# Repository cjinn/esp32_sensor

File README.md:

# ESP32 Sensor Module
This repository outlines an attempt to make a universal ESP32 board to conduct IoT projects with the help of sensors. As such, it is highly customisable and will most likely undergo many revisions.

The goal is to have multiple of these ESP32 sensor modules interact with each other using mesh Wi-Fi to share information with each other.

# Table of Contents
- [ESP32 Sensor Module](#esp32-sensor-module)
- [Table of Contents](#table-of-contents)
- [Hardware Versions](#hardware-versions)
  - [v0.0.3b](#v003b)
    - [v0.0.3c](#v003c)
    - [Known Hardware Issues](#known-hardware-issues)
- [Acknowledgements](#acknowledgements)

# Hardware Versions
Each hardware revision will be updated and the version as such. This version system is adopted from v0.0.4 onwards. The convection is as follows:

X.Y.ZA
- X: Major version number of the design. It is assumed there are major changes to the overall design including PCB, components, fucntionality, purpose, etc.
- Y: Minor version number of the design. Any increment on this signifies a minor design revision. Most likely an electrical characteristic change and/or component replacement.
- Z: Revision version number of the design. Any increment on this signifies a commit has been made to the design. Most likely adjustments to facilitate assembly houses, manufacturing and production.
- A: Alphabetical designation. Used to indicate even more minor adjustments like spelling mistakes and refreshing files.

## v0.0.3b
Originally a 4-layer PCB, it was redesigned to a 2-layer PCB in order to meet capstone project deadlines and it is the first iteration that was manufactured, tested and worked (well, most of it anyways). As such, it is noticebly bare-bones and has hardware design flaws. It is not recommended to go with this.

### v0.0.3c
Refreshed gerber files, schematics and BOM to be packaged such that it can be used to shop around between assembly houses. No meaningful changes since v0.0.3b.

### Known Hardware Issues
- [IMU SDA pin interferes with ESP32 boot up](https://github.com/cjinn/esp32_sensor/issues/2)
- [Crystal Oscillator missing from Hardware Design](https://github.com/cjinn/esp32_sensor/issues/1)

# Acknowledgements
Thanks to Isaac Tan for helping me design, test and realise this project from the very beginning.

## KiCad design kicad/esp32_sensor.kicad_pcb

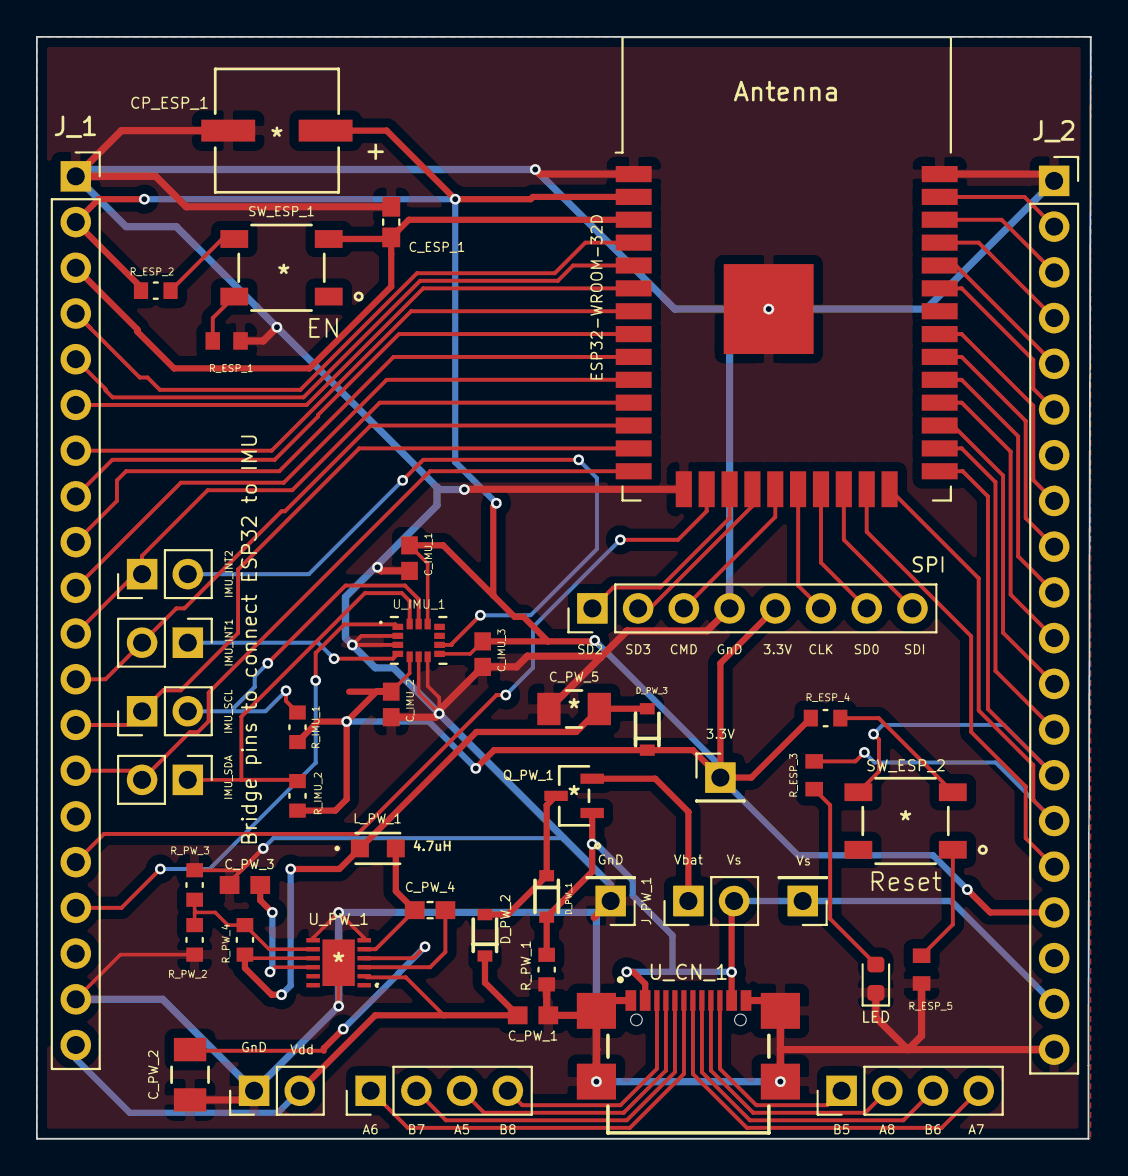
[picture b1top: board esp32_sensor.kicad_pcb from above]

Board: 2 copper layers, 58.5 x 61.2 mm, 47 parts (0 on the bottom side), 63 nets.

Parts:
CP_ESP_1: 100uF; UCB0J101MCL1GS
C_ESP_1: 0.1uF; CAPC1608X90
C_IMU_1, C_IMU_2, C_IMU_3: 100nF; CAPC1608X90N
C_PW_1, C_PW_3: 1uF; 0603
C_PW_2, C_PW_5: 4.7uF; C1206C475K3RACAUTO
C_PW_4: 0.1uF; CAPC1608X90
D_PW_1, D_PW_2, D_PW_3: BAT20JFILM
J_1, J_2: 4157; PinSocket_1x20_P2.54mm_Vertical
J_3: SPI; PinHeader_1x08_P2.54mm_Vertical
J_4: IMU_INT2; PinHeader_1x02_P2.54mm_Vertical
J_5: IMU_INT1; PinHeader_1x02_P2.54mm_Vertical
J_6: IMU_SCL; PinHeader_1x02_P2.54mm_Vertical
J_7: IMU_SDA; PinHeader_1x02_P2.54mm_Vertical
J_CN_1, J_CN_2: Header_Pin_4; PinHeader_1x04_P2.54mm_Vertical
J_CN_3, J_CN_4: Header_Pin_1; PinHeader_1x01_P2.54mm_Vertical
J_PW_1, J_PW_2: Header_Pin_2; PinHeader_1x02_P2.54mm_Vertical
J_PW_3: Header_Pin_1; PinHeader_1x01_P2.54mm_Vertical
LED_ESP_1: LED; LED_0603_1608Metric
L_PW_1: 4.7uH; CV201210-4R7K
Q_PW_1: IRLML5103TRPBF
R_ESP_1, R_ESP_3, R_ESP_5: 500; RESC1508X55N
R_ESP_2, R_ESP_4: 10k; RESC1608X55N
R_IMU_1, R_IMU_2: 4.7k; RESC1608X55N
R_PW_1: 10k; RESC1608X55N
R_PW_2, R_PW_3: 100k; RESC1608X55N
R_PW_4: 115k; RESC1608X55N
SW_ESP_1, SW_ESP_2: PTS647SK38SMTR2LFS
U_CN_1: USB4110-GF-A
U_ESP_1: ESP32-WROOM-32D; ESP32-WROOM-32
U_IMU_1: LSM6DSMTR
U_PW_1: MAX25276ATCA_VY+; MAX25276ATCAVY

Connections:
+3V3: CP_ESP_1.1, C_IMU_1.1, C_IMU_2.1, C_IMU_3.1, D_PW_3.C, J_1.2, J_2.17, J_3.5, J_PW_3.1, R_ESP_2.1, R_ESP_4.2, R_IMU_1.2, R_IMU_2.1, U_ESP_1.2, U_IMU_1.5, U_IMU_1.8, U_IMU_1.12
+BATT: J_PW_1.1, Q_PW_1.2
/ESP32 Chip/ESP32_EN: C_ESP_1.1, J_1.3, SW_ESP_1.3, U_ESP_1.3
/ESP32 Chip/ESP32_Pin4: J_1.4, U_ESP_1.4
/ESP32 Chip/ESP32_Pin5: J_1.5, U_ESP_1.5
/ESP32 Chip/ESP32_Pin6: J_1.6, U_ESP_1.6
/ESP32 Chip/ESP32_Pin7: J_1.7, U_ESP_1.7
/ESP32 Chip/ESP32_Pin8: J_1.8, U_ESP_1.8
/ESP32 Chip/ESP32_Pin9: J_1.9, U_ESP_1.9
/ESP32 Chip/ESP32_Pin10: J_1.10, U_ESP_1.10
/ESP32 Chip/ESP32_Pin11: J_1.11, J_4.1, U_ESP_1.11
/ESP32 Chip/ESP32_Pin12: J_1.12, J_5.2, U_ESP_1.12
/ESP32 Chip/ESP32_Pin13: J_1.13, J_6.1, U_ESP_1.13
/ESP32 Chip/ESP32_Pin14: J_1.14, J_7.2, U_ESP_1.14
/ESP32 Chip/ESP32_Pin16: J_1.16, U_ESP_1.16
/ESP32 Chip/ESP32_Pin17: J_3.1, U_ESP_1.17
/ESP32 Chip/ESP32_Pin18: J_3.2, U_ESP_1.18
/ESP32 Chip/ESP32_Pin19: J_3.3, U_ESP_1.19
/ESP32 Chip/ESP32_Pin20: J_3.6, U_ESP_1.20
/ESP32 Chip/ESP32_Pin21: J_3.7, U_ESP_1.21
/ESP32 Chip/ESP32_Pin22: J_3.8, U_ESP_1.22
/ESP32 Chip/ESP32_Pin23: J_2.16, U_ESP_1.23
/ESP32 Chip/ESP32_Pin24: J_2.15, R_ESP_3.1, U_ESP_1.24
/ESP32 Chip/ESP32_Pin25: J_2.14, SW_ESP_2.4, U_ESP_1.25
/ESP32 Chip/ESP32_Pin26: J_2.13, U_ESP_1.26
/ESP32 Chip/ESP32_Pin27: J_2.12, U_ESP_1.27
/ESP32 Chip/ESP32_Pin28: J_2.11, U_ESP_1.28
/ESP32 Chip/ESP32_Pin29: J_2.10, U_ESP_1.29
/ESP32 Chip/ESP32_Pin30: J_2.9, U_ESP_1.30
/ESP32 Chip/ESP32_Pin31: J_2.8, U_ESP_1.31
/ESP32 Chip/ESP32_Pin33: J_2.6, U_ESP_1.33
/ESP32 Chip/ESP32_Pin36: J_2.3, U_ESP_1.36
/ESP32 Chip/ESP32_Pin37: J_2.2, U_ESP_1.37
/ESP32 Chip/ESP32_RX0: J_2.5, U_ESP_1.34
/ESP32 Chip/ESP32_TX0: J_2.4, U_ESP_1.35
/IMU/IMU_INT1: J_5.1, U_IMU_1.4
/IMU/IMU_INT2: J_4.2, U_IMU_1.9
/IMU/IMU_SCL: J_6.2, R_IMU_1.1, U_IMU_1.13
/IMU/IMU_SDA: J_7.1, R_IMU_2.2, U_IMU_1.14
/IMU/IMU_SDO_SAO: J_1.17, U_IMU_1.1
GND: CP_ESP_1.2, C_ESP_1.2, C_IMU_1.2, C_IMU_2.2, C_IMU_3.2, C_PW_1.1, C_PW_2.2, C_PW_3.1, C_PW_5.2, J_1.1, J_1.19, J_2.1, J_2.20, J_3.4, J_CN_4.1, J_PW_2.1, LED_ESP_1.1, R_ESP_1.2, R_ESP_5.2, R_PW_1.2, R_PW_2.1, R_PW_3.1, U_CN_1.A1/B12, U_CN_1.B1/A12, U_CN_1.S1, U_CN_1.S2, U_CN_1.S3, U_CN_1.S4, U_ESP_1.1, U_ESP_1.15, U_ESP_1.38, U_ESP_1.39, U_IMU_1.2, U_IMU_1.3, U_IMU_1.6, U_IMU_1.7, U_PW_1.6, U_PW_1.7, U_PW_1.13
unnamed: C_PW_2.1, U_PW_1.4
unnamed: C_PW_3.2, U_PW_1.10
unnamed: C_PW_4.1, L_PW_1.2, U_PW_1.5
unnamed: C_PW_4.2, U_PW_1.3
unnamed: C_PW_5.1, D_PW_3.A, L_PW_1.1, R_PW_4.1, U_PW_1.9
unnamed: D_PW_1.C, D_PW_2.A, Q_PW_1.3
unnamed: J_CN_1.1, U_CN_1.B5
unnamed: J_CN_1.2, U_CN_1.A8
unnamed: J_CN_1.3, U_CN_1.B6
unnamed: J_CN_1.4, U_CN_1.A7
unnamed: J_CN_2.1, U_CN_1.A6
unnamed: J_CN_2.2, U_CN_1.B7
unnamed: J_CN_2.3, U_CN_1.A5
unnamed: J_CN_2.4, U_CN_1.B8
unnamed: LED_ESP_1.2, R_ESP_3.2
unnamed: R_ESP_1.1, SW_ESP_1.2
unnamed: R_ESP_2.2, SW_ESP_1.4
unnamed: R_ESP_4.1, SW_ESP_2.3
unnamed: R_ESP_5.1, SW_ESP_2.1
unnamed: R_PW_2.2, R_PW_3.2, R_PW_4.2, U_PW_1.8
VDD: C_PW_1.2, D_PW_2.C, J_1.20, J_PW_2.2, U_PW_1.2
VS: D_PW_1.A, J_2.19, J_CN_3.1, J_PW_1.2, Q_PW_1.1, R_PW_1.1, U_CN_1.A4/B9, U_CN_1.B4/A9

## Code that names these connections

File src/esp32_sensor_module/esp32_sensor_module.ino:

/**
   ESP32 Sensor Module


   Reference: https://github.com/arduino-libraries/Arduino_LSM6DS3/blob/master/src/LSM6DS3.cpp
*/

/**
   Metadata
*/
#define SW_VERSION "0.0.1"
#define HW_VERSION "0.0.3b"

/**
   Libraries
*/
#include "Wire.h" // ESP32 Wire.h

/**
   ESP32 Pins
*/
#define IMU_INT2      26 // Pin 11
#define IMU_INT1      27 // Pin 12  
#define IMU_SCL       14 // Pin 13
#define IMU_SDA       12 // Pin 14
//#define IMU_SD0       // Not implemented

/**
   LSM Registers
*/
#define LSM6DSM_ADDRESS             0x6B // SD0 should not be connected

#define LSM6DSM_WHO_AM_I_REG        0X0F
#define WHO_AM_I_REG_VALUE          0x6A

#define LSM6DSM_CTRL1_XL            0X10
#define LSM6DSM_CTRL2_G             0X11
#define LSM5DSM_CTRL3_C             0X12

#define LSM6DSM_STATUS_REG          0X1E

#define LSM6DSM_CTRL6_C             0X15
#define LSM6DSM_CTRL7_G             0X16
#define LSM6DSM_CTRL8_XL            0X17

#define LSM6DSM_OUTX_L_G            0X22
#define LSM6DSM_OUTX_H_G            0X23
#define LSM6DSM_OUTY_L_G            0X24
#define LSM6DSM_OUTY_H_G            0X25
#define LSM6DSM_OUTZ_L_G            0X26
#define LSM6DSM_OUTZ_H_G            0X27

#define LSM6DSM_OUTX_L_XL           0X28
#define LSM6DSM_OUTX_H_XL           0X29
#define LSM6DSM_OUTY_L_XL           0X2A
#define LSM6DSM_OUTY_H_XL           0X2B
#define LSM6DSM_OUTZ_L_XL           0X2C
#define LSM6DSM_OUTZ_H_XL           0X2D

/**
   Constants
*/
#define SERIAL_BAUD_RATE          115200

/**
   Variables
*/

void setup() {
  Serial.begin(SERIAL_BAUD_RATE);
  Serial.println("Wait for user to be ready");
  while (true) {

    if (Serial.available() > 0) {
      if (Serial.read() == 'G') {
        break;
      }
    }
  }

  imuSetup();
}

void imuSetup(void) {
  Wire.begin(IMU_SDA, IMU_SCL);

  while (readRegister(LSM6DSM_WHO_AM_I_REG) != 0x6A) {
    Serial.println("Unable to talk to IMU! Trying again!");
    delay(1000);
  }

  /**
     Taken from LSM library
  */
  //set the gyroscope control register to work at 104 Hz, 2000 dps and in bypass mode
  writeRegister(LSM6DSM_CTRL2_G, 0x4C);

  // Set the Accelerometer control register to work at 104 Hz, 4G,and in bypass mode and enable ODR/4
  // low pass filter(check figure 9 on LSM6DSM's datasheet)
  writeRegister(LSM6DSM_CTRL1_XL, 0x4A); // I think this is correct??

  // set gyroscope power mode to high performance and bandwidth to 16 MHz
  writeRegister(LSM6DSM_CTRL7_G, 0x00);

  // Set the ODR config register to ODR/4
  writeRegister(LSM6DSM_CTRL8_XL, 0xA4); // I think this is correct??

  Serial.println("Ready");
}

int writeRegister(uint8_t address, uint8_t value)
{
  Wire.beginTransmission(LSM6DSM_ADDRESS);
  Wire.write(address);
  Wire.write(value);
  if (Wire.endTransmission() != 0) {
    return 0;
  }

  return 1;
}

int readRegister(uint8_t address) {
  uint8_t value;

  if (readRegisters(address, &value, sizeof(value)) != 1) {
    return -1;
  }

  return value;
}

int readRegisters(uint8_t address, uint8_t* data, size_t length) {
  Wire.beginTransmission(LSM6DSM_ADDRESS);
  Wire.write(address);

  if (Wire.endTransmission(false) != 0) {
    return -1;
  }

  if (Wire.requestFrom(LSM6DSM_ADDRESS, length) != length) {
    return 0;
  }

  for (size_t i = 0; i < length; i++) {
    *data++ = Wire.read();
  }

  return 1;
}

int gyroscopeAvailable() {
  if (readRegister(LSM6DSM_STATUS_REG) & 0x02) {
    return 1;
  }

  return 0;
}

int accelerationAvailable() {
  if (readRegister(LSM6DSM_STATUS_REG) & 0x01) {
    return 1;
  }

  return 0;
}

int readGyroscope(float& x, float& y, float& z) {
  int16_t data[3];

  if (!readRegisters(LSM6DSM_OUTX_L_G, (uint8_t*)data, sizeof(data))) {
    x = NAN;
    y = NAN;
    z = NAN;

    return 0;
  }

  x = data[0] * 2000.0 / 32768.0;
  y = data[1] * 2000.0 / 32768.0;
  z = data[2] * 2000.0 / 32768.0;

  return 1;
}

/**
   Needs work
*/
int readAcceleration(float& x, float& y, float& z) {
  int16_t data[3];

  if (!readRegisters(LSM6DSM_OUTX_L_XL, (uint8_t*)data, sizeof(data))) {
    x = NAN;
    y = NAN;
    z = NAN;

    return 0;
  }

  x = data[0] * 4.0 / 32768.0;
  y = data[1] * 4.0 / 32768.0;
  z = data[2] * 4.0 / 32768.0;

  return 1;
}

void loop() {
  float x, y, z;
  
  if (gyroscopeAvailable()) {
    readGyroscope(x, y, z);

    Serial.print("Gyroscope: ");
    Serial.print(x);
    Serial.print('\t');
    Serial.print(y);
    Serial.print('\t');
    Serial.println(z);
  }

    if (accelerationAvailable()) {
    readAcceleration(x, y, z);

    Serial.print("Acceleration: ");
    Serial.print(x);
    Serial.print('\t');
    Serial.print(y);
    Serial.print('\t');
    Serial.println(z);
  }

  delay(100);
}

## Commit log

2020-11-23 Created initial draft of ESP32 sensor module
2020-11-23 Deleted a header pin. Started working on PCB
2020-11-23 Created PCB design for ESP32 sensor for v0.0.1. Exported PDFs and gerber files
2020-11-25 Updated .gitignore to ignore compressed files
2020-11-25 Added ESP32 datasheets
2020-11-25 Added power regulator and imu datasheets
2020-11-25 Updated schematic and PCB design to v0.0.2 for 2-layer pcb. Added more silkscreen text
2020-11-25 Updated sensor module and PCB design to v0.0.3. Fixed design issues with USB. Updated via size to 0.6mm. Moved polarised capacitor towards inside the board
2020-11-25 Fixed silkscreen to display properly. Moved header pin silkscreen to bottom
2020-11-25 Updated PCB to v0.0.3b. Fixed tracks and silkscreen.
2020-12-02 Implemented ESP32 Arduino software that extracts the gyroscope and acceleration data
2020-12-03 Begun implementing ESPNOW and WiFi functionality. Updated BOM.ini
2021-04-01 Re-exported KiCAD PCB files for assembly house/manufacturing. Updated README.md. Included BOM list
